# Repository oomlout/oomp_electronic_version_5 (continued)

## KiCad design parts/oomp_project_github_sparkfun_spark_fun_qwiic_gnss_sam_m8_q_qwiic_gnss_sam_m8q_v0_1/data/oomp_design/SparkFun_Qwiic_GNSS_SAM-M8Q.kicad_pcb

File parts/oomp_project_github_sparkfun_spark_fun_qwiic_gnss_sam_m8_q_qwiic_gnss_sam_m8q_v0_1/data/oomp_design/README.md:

# OOMP KiCad design copy

Open `SparkFun_Qwiic_GNSS_SAM-M8Q.kicad_pro` (or the `.kicad_pcb` / `.kicad_sch`) in KiCad. Local OOMP libraries are under `libraries/`. Original inputs are preserved in [../original/](../original/).

Only verified unchanged installed KiCad defaults were renamed. Modified, custom, unmatched and unavailable items remain unchanged. Soldering variants are never swapped during conversion. Existing pad coordinates, nets and UUIDs are preserved.

See [conversion_report.yaml](conversion_report.yaml) for every conversion and skip. Copy this directory before editing; regeneration refuses to overwrite edited design files.

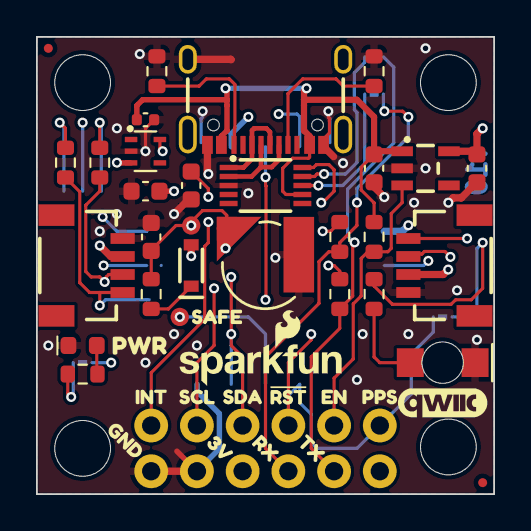
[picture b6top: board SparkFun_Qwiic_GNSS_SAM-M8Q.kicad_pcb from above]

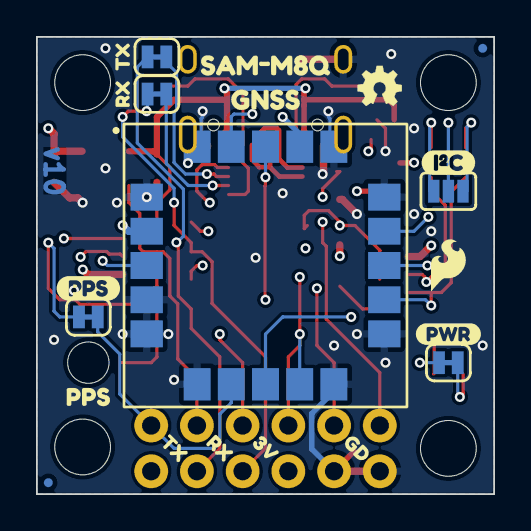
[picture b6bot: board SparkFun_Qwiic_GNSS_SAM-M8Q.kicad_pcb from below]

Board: 4 copper layers, 25.4 x 25.4 mm, 70 parts (21 on the bottom side), 29 nets.

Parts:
BT1: ML414H; ML414H_IV01E
C1, C9: 1.0uF; C_0603_1608Metric
C10: 10uF; C_0603_1608Metric
C11, C14: 0.1uF; C_0603_1608Metric
D1: Red; LED_0603_1608Metric_Red
D2: Green; LED_1206_Bottom_Green
D3: PESD0402; C_0402_1005Metric
D5: PMEG4005EJ; SOD-323
D7: PESD3V3L4UG; SOT-353
FID1, FID2, FID3, FID4: Fiducial_0.5mm; Fiducial_0.5mm_Mask1mm
G4: OSHW_Logo; Creative_Commons_License
J1, J2: Qwiic_RA; JST_1x04_P1.0mm_Horizontal_SMD
J4: USB_C_Receptacle; USB-C_16
J6, J7: Conn_01x06; 1x06_P2.54mm
JP1: LED; Jumper_2_NC_Trace
JP2: I2C; Jumper_3_NO
JP3: PPS; Jumper_2_NC_Trace
JP4: RX; Jumper_2_NC_Trace
JP5: TX; Jumper_2_NC_Trace
R2, R4: 5.1k; R_0603_1608Metric
R3: 4.7k; R_0603_1608Metric
R5, R6, R8: 2.2k; R_0603_1608Metric
R7: 1k; R_0603_1608Metric
R10: 100k; R_0603_1608Metric
R11, R12: 470; R_0603_1608Metric
Ref**: Val**; OSHW_Logo_2.5mm
ST1, ST2, ST3, ST4: Standoff
TP1: TestPoint_0.75mm; TestPoint-1.0mm
TP3: 0.75mm; TestPoint-1.0mm
U1: SAM-M8Q; u-blox_SAM-M8Q
U4: CH340E; MSOP-10_3x3mm_P0.5mm
U6: RT9080-3.3; SOT23-5
kibuzzard-68A62ADB: G***; kibuzzard-68A62ADB
kibuzzard-68A62B00: G***; kibuzzard-68A62B00
kibuzzard-68A543C0: G***; kibuzzard-68A543C0
kibuzzard-68A543C6: G***; kibuzzard-68A543C6
kibuzzard-68A543D0: G***; kibuzzard-68A543D0
kibuzzard-68A543D8: G***; kibuzzard-68A543D8
kibuzzard-68A5438E: G***; kibuzzard-68A5438E
kibuzzard-68A6334A: G***; kibuzzard-68A6334A
kibuzzard-68B26D79: G***; kibuzzard-68B26D79
kibuzzard-68B65C4A: G***; kibuzzard-68B65C4A
kibuzzard-68B657DC: G***; kibuzzard-68B657DC
kibuzzard-68B657F6: G***; kibuzzard-68B657F6
kibuzzard-68B657FC: G***; kibuzzard-68B657FC
kibuzzard-68B2754E, kibuzzard-68B2754E#2: G***; kibuzzard-68B2754E
kibuzzard-68B2766E: G***; kibuzzard-68B2766E
kibuzzard-68B27525, kibuzzard-68B27525#2: G***; kibuzzard-68B27525
kibuzzard-68B65800: G***; kibuzzard-68B65800
kibuzzard-68B65805: G***; kibuzzard-68B65805
kibuzzard-68F7EB4F: G***; kibuzzard-68F7EB4F
kibuzzard-68F7EE97: G***; kibuzzard-68F7EE97
kibuzzard-68F7EEC6: G***; kibuzzard-68F7EEC6
kibuzzard-68F83B37: G***; kibuzzard-68F83B37

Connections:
3.3V: C10.1, C11.1, D5.2 (A), D7.3 (K2), J1.2, J2.2, J7.4, JP1.2 (B), JP2.2 (B), U1.2 (VCC_IO), U1.17 (VCC), U6.5 (VOUT)
EN: J6.5, R10.1, U6.3 (EN)
EXTINT: J6.1, U1.19 (EXTINT)
GND: BT1.-, C1.2, C9.2, C10.2, C11.2, C14.2, D1.1 (K), D2.1 (K), D3.1 (A1), D7.2 (A), J1.1, J2.1, J4.GND, J4.S (SHIELD), J7.5, J7.6, R2.1, R4.1, U1.1 (GND), U1.4 (GND), U1.5 (GND), U1.6 (GND), U1.10 (GND), U1.11 (GND), U1.15 (GND), U1.16 (GND), U1.20 (GND), U4.3 (GND), U6.2 (GND)
unnamed: D1.2 (A), R3.1
unnamed: D2.2 (A), R5.1
unnamed: D5.1 (K), R7.2
unnamed: J4.A5 (CC1), R4.2
unnamed: J4.B5 (CC2), R2.2
unnamed: JP1.1 (A), R3.2
unnamed: JP2.1 (A), R6.2
unnamed: JP2.3 (C), R8.2
unnamed: JP3.1 (A), R5.2
unnamed: JP4.1 (A), U4.8 (TXD)
unnamed: JP5.1 (A), U4.9 (RXD)
unnamed: R11.1, U1.14 (RXD)
unnamed: R12.1, U1.13 (TXD)
unnamed: J4.A6 (D+), J4.B6 (D+), U4.1 (UD+)
unnamed: J4.A7 (D-), J4.B7 (D-), U4.2 (UD-)
unnamed: C14.1, U4.10 (V3)
PPS: J6.6, JP3.2 (B), U1.7 (TIMEPULSE)
RX: J7.3, JP4.2 (B), R11.2
SCL: J1.4, J2.4, J6.2, R6.1, U1.12 (SCL)
SDA: J1.3, J2.3, J6.3, R8.1, U1.9 (SDA)
TX: J7.2, JP5.2 (B), R12.2
VBUS: C1.1, D3.2 (A2), J4.VBUS, R10.2, U4.7 (VCC), U6.1 (VIN)
V_BCKP: BT1.+, C9.1, D7.5 (K4), R7.1, TP1.1, U1.3 (V_BCKP)
~RST: J6.4, U1.18 (~RESET)
~SAFE: TP3.1, U1.8 (~SAFEBOOT)

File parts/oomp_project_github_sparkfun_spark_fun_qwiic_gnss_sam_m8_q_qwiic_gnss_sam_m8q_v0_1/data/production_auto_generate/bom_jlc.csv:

Comment,Designator,Footprint,LCSC Part #
0.1uF,"C11,C14",SparkFun-Capacitor:C_0603_1608Metric,C14663
0.75mm,TP3,SparkFun-Connector:TestPoint-1.0mm,
1.0uF,"C1,C9",SparkFun-Capacitor:C_0603_1608Metric,C5673
100k,R10,SparkFun-Resistor:R_0603_1608Metric,C25803
10uF,C10,SparkFun-Capacitor:C_0603_1608Metric,C19702
1k,R7,SparkFun-Resistor:R_0603_1608Metric,C2907002
2.2k,"R5,R6,R8",SparkFun-Resistor:R_0603_1608Metric,C4190
4.7k,R3,SparkFun-Resistor:R_0603_1608Metric,C23162
470,"R11,R12",SparkFun-Resistor:R_0603_1608Metric,C23179
5.1k,"R2,R4",SparkFun-Resistor:R_0603_1608Metric,C23186
CH340E,U4,SparkFun-Semiconductor-Standard:MSOP-10_3x3mm_P0.5mm,
Conn_01x06,"J6,J7",SparkFun-Connector:1x06_P2.54mm,C37208
Green,D2,SparkFun-LED:LED_1206_Bottom_Green,
I2C,JP2,SparkFun-Jumper:Jumper_3_NO,
LED,JP1,SparkFun-Jumper:Jumper_2_NC_Trace,
ML414H,BT1,SparkFun-Battery:ML414H_IV01E,
PESD0402,D3,SparkFun-Capacitor:C_0402_1005Metric,C316059
PESD3V3L4UG,D7,SparkFun-Semiconductor-Standard:SOT-353,C70500
PMEG4005EJ,D5,SparkFun-Semiconductor-Standard:SOD-323,
PPS,JP3,SparkFun-Jumper:Jumper_2_NC_Trace,
Qwiic_RA,"J1,J2",SparkFun-Connector:JST_1x04_P1.0mm_Horizontal_SMD,C160404
Red,D1,SparkFun-LED:LED_0603_1608Metric_Red,
RT9080-3.3,U6,SparkFun-Semiconductor-Standard:SOT23-5,
RX,JP4,SparkFun-Jumper:Jumper_2_NC_Trace,
SAM-M8Q,U1,SparkFun-GNSS:u-blox_SAM-M8Q,
TestPoint_0.75mm,TP1,SparkFun-Connector:TestPoint-1.0mm,
TX,JP5,SparkFun-Jumper:Jumper_2_NC_Trace,
USB_C_Receptacle,J4,SparkFun-Connector:USB-C_16,C2765186
